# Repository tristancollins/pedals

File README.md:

# My Pedal Source Files
I've moved these to their own repos under my account...

KiCAD files for my pedal builds

- Merlin's Engineer's Thumb Compressor / Sustainer
- Merlin's GlassBlower

Also included are BoMs and Gerbers.

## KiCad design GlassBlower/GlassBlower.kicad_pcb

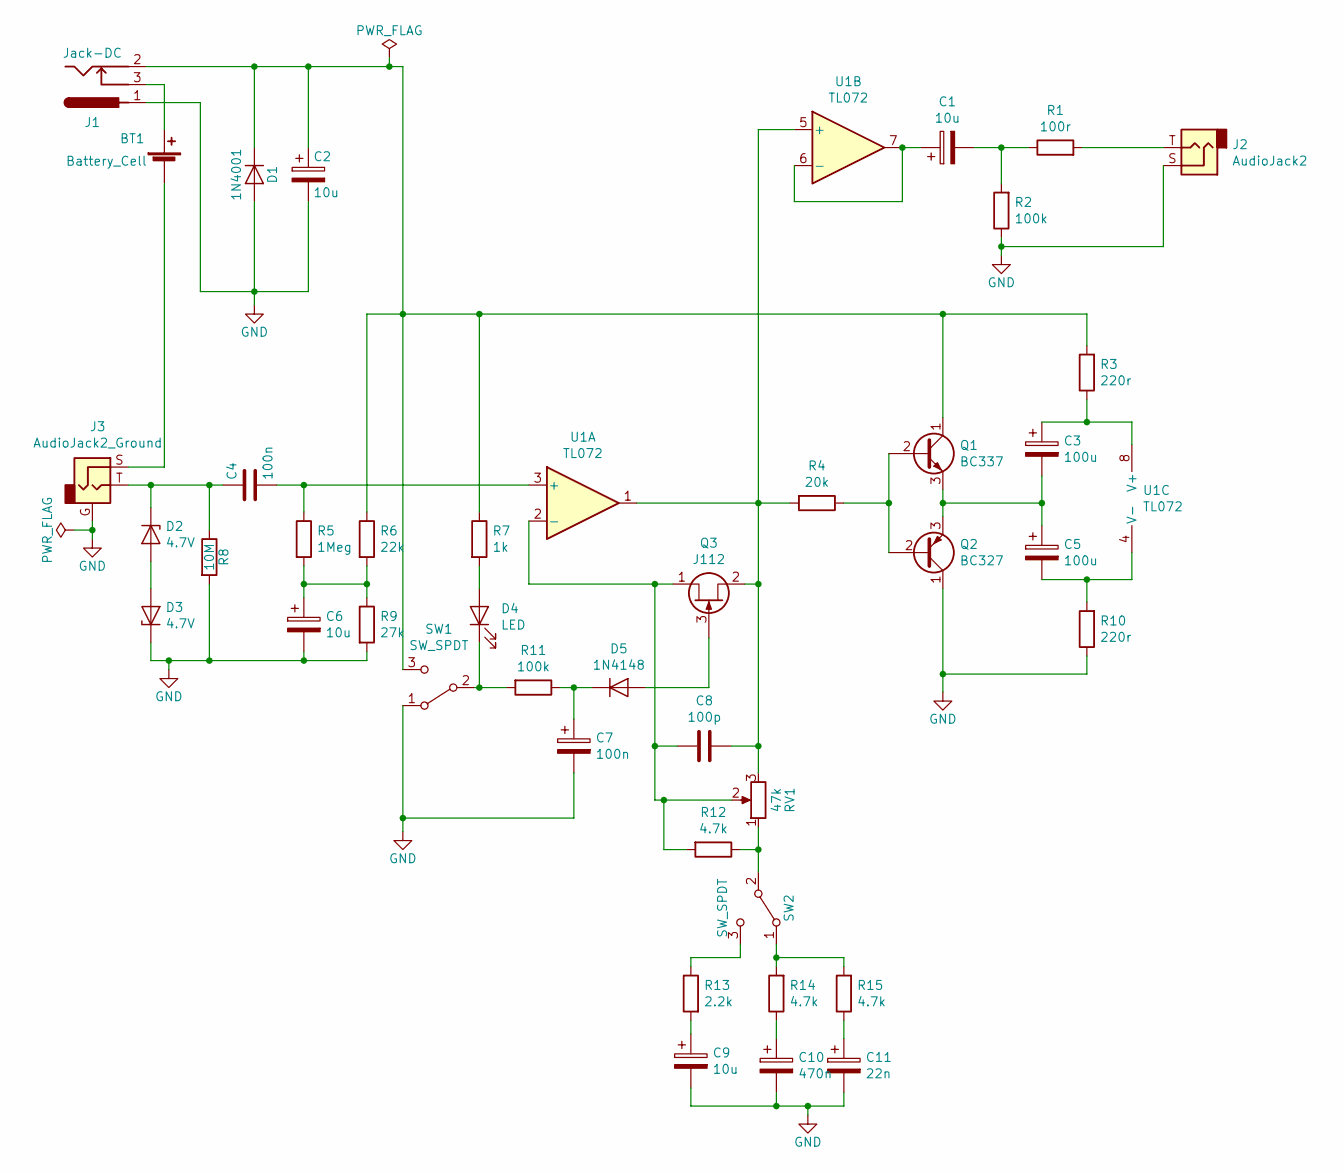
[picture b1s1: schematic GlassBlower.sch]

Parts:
BT1: Battery_Cell; SolderWirePad_1x02_P3.81mm_Drill1.2mm; MPN 36-232-ND
C1, C2, C6, C9: 10u; CP_Radial_D5.0mm_P2.50mm; MPN P19549CT-ND
C3, C5: 100u; CP_Radial_D5.0mm_P2.50mm; MPN 493-12902-1-ND
C4, C7: 100n; C_Disc_D5.0mm_W2.5mm_P5.00mm-TC; MPN 399-5444-1-ND
C8: 100p; C_Disc_D5.0mm_W2.5mm_P5.00mm-TC; MPN 445-173472-1-ND
C10: 470n; C_Disc_D5.0mm_W2.5mm_P5.00mm-TC; MPN 399-11865-1-ND
C11: 22n; C_Disc_D5.0mm_W2.5mm_P5.00mm-TC; MPN 399-5451-1-ND
D1: 1N4001; D_DO-35_SOD27_P7.62mm_Horizontal; MPN 641-1310-1-ND
D2, D3: 4.7V; D_DO-35_SOD27_P7.62mm_Horizontal; MPN 1N5230BFSCT-ND
D4: LED; LED_D3.0mm; MPN 732-5005-ND
D5: 1N4148; D_DO-35_SOD27_P7.62mm_Horizontal; MPN 1N4148FS-ND
J1: Jack-DC; BARREL_JACK; MPN PJ-002B
J2: AudioJack2; SolderWirePad_1x02_P3.81mm_Drill1.2mm
J3: AudioJack2_Ground; SolderWirePad_1x03_P3.81mm_Drill1.2mm
Q1: BC337; TO-92_HandSolder; MPN BC33725BU-ND
Q2: BC327; TO-92_HandSolder; MPN BC327OS-ND
Q3: J112; TO-92_HandSolder; MPN J112FS-ND
R1: 100r; R_Axial_DIN0207_L6.3mm_D2.5mm_P7.62mm_Horizontal; MPN 100XBK-ND
R2, R11: 100k; R_Axial_DIN0207_L6.3mm_D2.5mm_P7.62mm_Horizontal; MPN 100KXBK-ND
R3, R10: 220r; R_Axial_DIN0207_L6.3mm_D2.5mm_P7.62mm_Horizontal; MPN 221XBK-ND
R4: 20k; R_Axial_DIN0207_L6.3mm_D2.5mm_P7.62mm_Horizontal; MPN 20.0KXBK-ND
R5: 1Meg; R_Axial_DIN0207_L6.3mm_D2.5mm_P7.62mm_Horizontal; MPN 1.00MXBK-ND
R6: 22k; R_Axial_DIN0207_L6.3mm_D2.5mm_P7.62mm_Horizontal; MPN 22.1KXBK-ND
R7: 1k; R_Axial_DIN0207_L6.3mm_D2.5mm_P7.62mm_Horizontal; MPN 1.00KXBK-ND
R8: 10M; R_Axial_DIN0207_L6.3mm_D2.5mm_P7.62mm_Horizontal; MPN CF14JT10M0CT-ND
R9: 27k; R_Axial_DIN0207_L6.3mm_D2.5mm_P7.62mm_Horizontal; MPN 27.4KXBK-ND
R12, R14, R15: 4.7k; R_Axial_DIN0207_L6.3mm_D2.5mm_P7.62mm_Horizontal; MPN 4.64KXBK-ND
R13: 2.2k; R_Axial_DIN0207_L6.3mm_D2.5mm_P7.62mm_Horizontal; MPN 2.21KXBK-ND
RV1: 47k; Potentiometer_PCB_rightangle
SW1: SW_SPDT; SolderWirePad_1x03_P3.81mm_Drill1.2mm; MPN EG5497-ND
SW2: SW_SPDT; SW_SubMicro_SPST; MPN EG2447-ND
U1: TL072; DIP-8_W7.62mm_Socket

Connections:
GND: C2.2, C6.2, C7.2, C9.2, C10.2, C11.2, D1.2 (A), D3.1 (K), J1.1, J2.S, J3.G, Q2.1 (C), R2.1, R8.2, R9.2, R10.1, SW1.1 (A)
unnamed: BT1.1 (+), J1.3
unnamed: BT1.2 (-), J3.S
unnamed: C1.1, U1.6 (-), U1.7
unnamed: C1.2, R1.1, R2.2
unnamed: C2.1, D1.1 (K), J1.2, Q1.1 (C), R3.2, R6.1, R7.1, SW1.3 (C)
unnamed: C3.1, R3.1, U1.8 (V+)
unnamed: C3.2, C5.1, Q1.3 (E), Q2.3 (E)
unnamed: C4.1, D2.1 (K), J3.T, R8.1
unnamed: C4.2, R5.1, U1.3 (+)
unnamed: C5.2, R10.2, U1.4 (V-)
unnamed: C6.1, R5.2, R6.2, R9.1
unnamed: C7.1, D5.1 (K), R11.1
unnamed: C8.1, Q3.2 (S), R4.2, RV1.3, U1.1, U1.5 (+)
unnamed: C8.2, Q3.1 (D), R12.2, RV1.2, U1.2 (-)
unnamed: C9.1, R13.2
unnamed: C10.1, R14.1
unnamed: C11.1, R15.1
unnamed: D2.2 (A), D3.2 (A)
unnamed: D4.1 (K), R11.2, SW1.2 (B)
unnamed: D4.2 (A), R7.2
unnamed: D5.2 (A), Q3.3 (G)
unnamed: J2.T, R1.2
unnamed: Q1.2 (B), Q2.2 (B), R4.1
unnamed: R12.1, RV1.1, SW2.2 (B)
unnamed: R13.1, SW2.3 (C)
unnamed: R14.2, R15.2, SW2.1 (A)

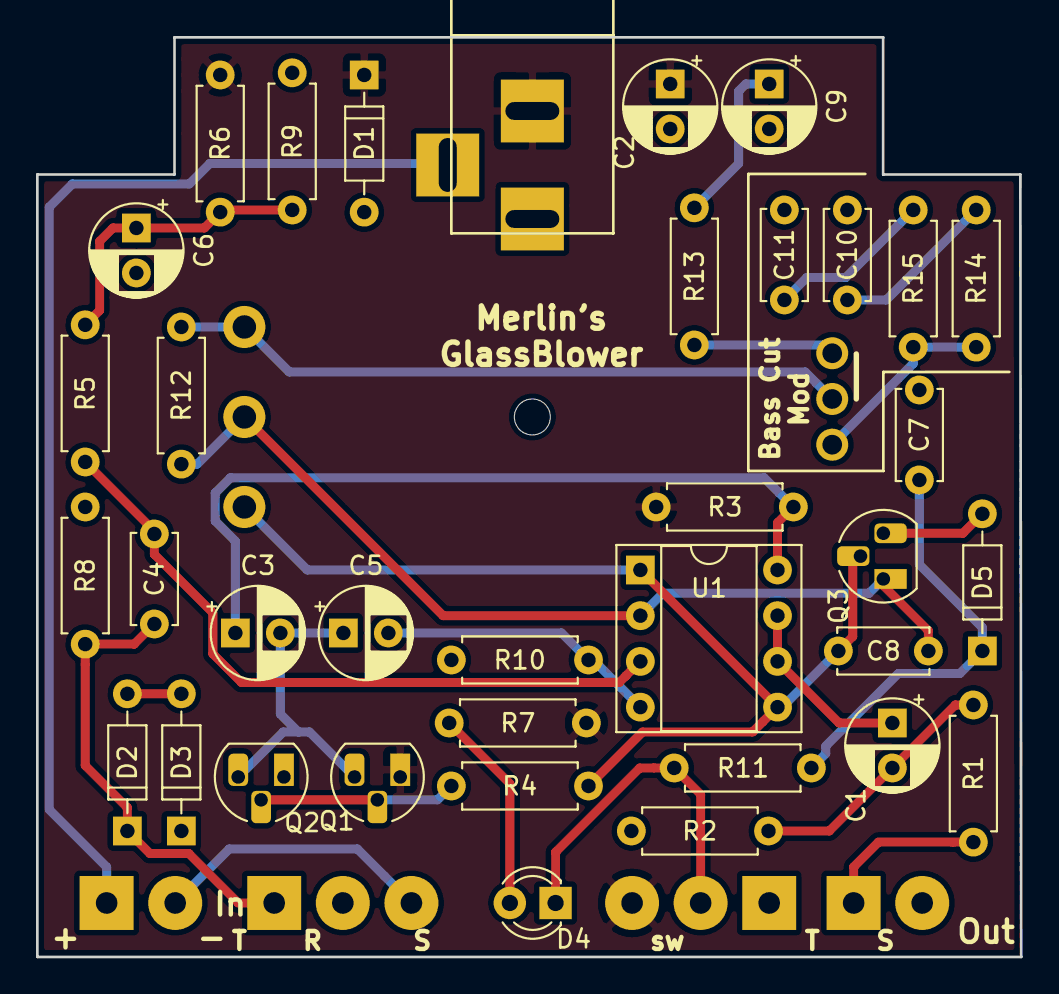
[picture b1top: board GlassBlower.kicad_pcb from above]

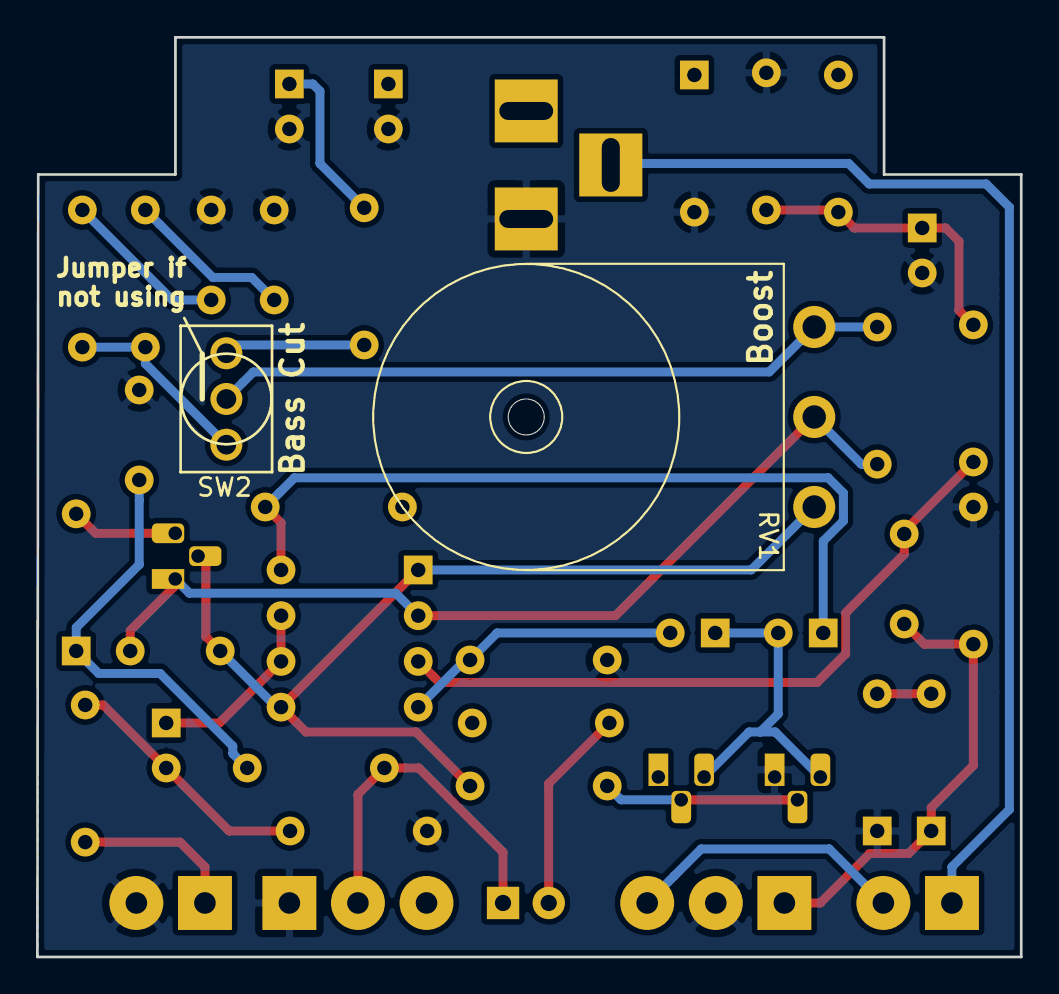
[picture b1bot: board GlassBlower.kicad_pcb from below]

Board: 2 copper layers, 54.7 x 51.1 mm, 42 parts (2 on the bottom side), 27 nets.

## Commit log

2020-04-25 EngineersThumb files added
2020-04-25 GlassBlower files added
2020-04-25 readme altered
2024-07-28 moving to own repos, update readme
